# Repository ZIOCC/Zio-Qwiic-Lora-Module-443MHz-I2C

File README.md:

# Zio-Qwiic-Lora-Module-443MHz-I2C

The gateway firmware referred [Sparkfun's QwiicRF](https://github.com/sparkfunx/Qwiic_RF)

> This product can be available for purchase [here](https://www.smart-prototyping.com/Zio-Qwiic-Lora-module-443MHz-I2C).

##### Description

This is a [Qwiic](https://www.smart-prototyping.com/Qwiic.html) version LoRa module, no soldering and jumper wire connections, just [Qwiic cable](https://www.smart-prototyping.com/zio-cables) plugin, and have fun! 

LoRa module is powerful, it can send and receive data packets at up to 10KM distance, and consumes very low power (10mA for receiver, 120mA for transmitter).

LoRa itself is a SPI device, in order to turn it into a I2C device, we added an MCU as the gateway to do the dirty work for you, you just need to use the module’s I2C interface to communicate with the others. It is just that easy.

> Note: This LoRa module is based on the LoRa-01 module, the frequency range is 420 - 450 MHz, check [here](https://www.thethingsnetwork.org/docs/lorawan/frequencies-by-country.html) to see if this can be used in your country.

##### Specification

* Voltage: 3.3V
* Interface: I2C
* I2C Address: 0x35, 0x36 (Default: 0x35)
* Distance: Up to 10KM
* Gateway MCU: ATMEGA328P
* Dimension: 26.0 x 41.6 mm
* Weight: 5.3g

##### Links

* [PCB Source file](https://github.com/ZIOCC/Zio-Qwiic-Lora-Module-443MHz-I2C/tree/master/EAGLE)
* [PCB schematic](https://github.com/ZIOCC/Zio-Qwiic-Lora-Module-443MHz-I2C/blob/master/zio%20qwiic%20lora%20module%20433%20schematic.pdf)
* [Demo code](https://github.com/sparkfun/SparkFun_QwiicRF_Library/)
* [Gateway firmware](https://github.com/ZIOCC/Zio-Qwiic-Lora-Module-443MHz-I2C/tree/master/Gateway_Firmware/Qwiic_RF_I2C_Pairing)

> ###### About Zio
> Zio is a new line of open sourced, compact, and grid layout boards, fully integrated for Arduino and Qwiic ecosystem. Designed ideally for wearables, robotics, small-space limitations or other on the go projects. Check out other awesome Zio products [here](https://www.smart-prototyping.com/Zio).

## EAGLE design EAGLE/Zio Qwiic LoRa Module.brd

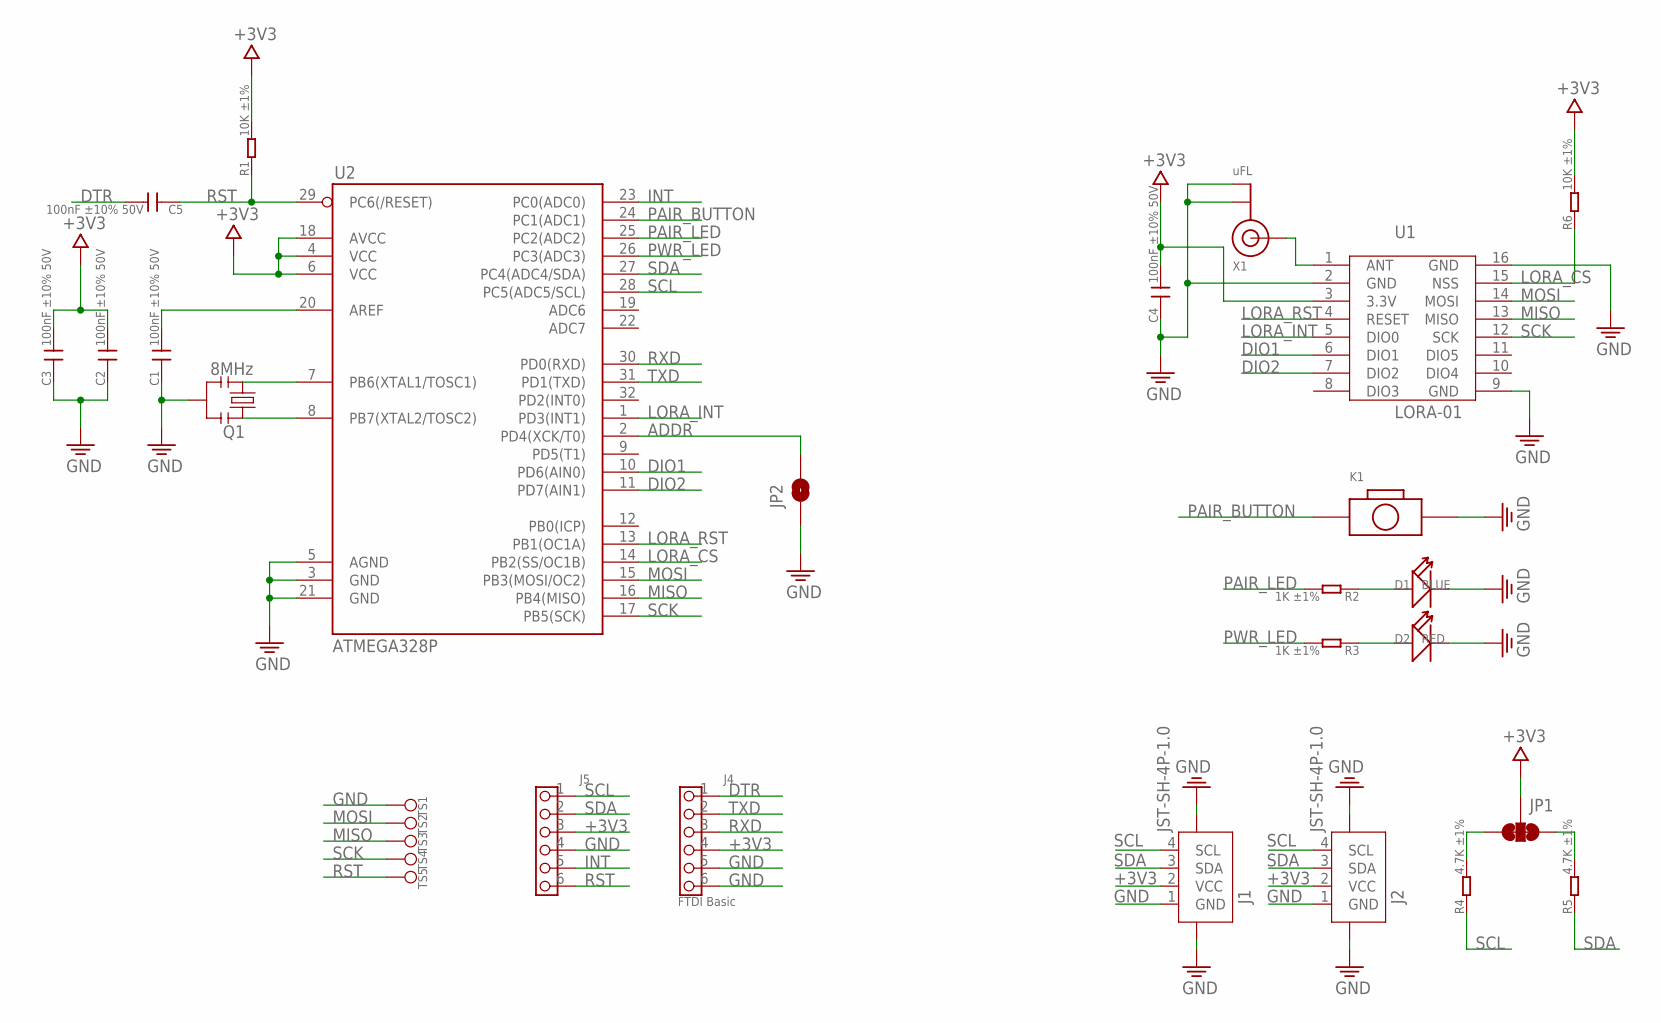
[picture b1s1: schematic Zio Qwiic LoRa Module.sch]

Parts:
C1, C2, C3, C4, C5: 100nF ±10% 50V; C0603
D1: BLUE; LED-0603
D2: RED; LED-0603
J1, J2: JST-SH-4P-1.0; JST-SH-4P
J4: FTDI Basic; 6P-2.54-60/35MIL
J5: HEADER-6P-60/35MIL; 6P-2.54-60/35MIL
JP1: SMT-JUMPER_3_2-NC_TRACE
JP2: JUMPER-SMT_2_NC_PASTE_NOCREM; SMT-JUMPER_2_NC_PASTE_SILK_NOCREM
K1: BOTTON-2PSKRKAEE020; SKRKAEE020
Q1: 8MHz; RESONATOR-SMD
R1, R6: 10K ±1%; R0603
R2, R3: 1K ±1%; R0603
R4, R5: 4.7K ±1%; R0603
TS1, TS2, TS3, TS4, TS5: TEST_POINT35MIL; 1P-35MIL
U1: LORA-01
U2: ATMEGA328P; TQFP32-08
X1: uFL; U.FL

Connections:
+3V3: C2.2, C3.2, C4.2, J1.2 (VCC), J2.2 (VCC), J4.4, J5.3, JP1.2, R1.2, R6.2, U1.3 (3.3V), U2.4 (VCC), U2.6 (VCC), U2.18 (AVCC)
ADDR: JP2.2, U2.2 (PD4(XCK/T0))
DIO1: U1.6 (DIO1), U2.10 (PD6(AIN0))
DIO2: U1.7 (DIO2), U2.11 (PD7(AIN1))
DTR: C5.2, J4.1
GND: C1.1, C2.1, C3.1, C4.1, D1.-, D2.-, J1.1 (GND), J1.NC1 (5), J1.NC2 (6), J2.1 (GND), J2.NC1 (5), J2.NC2 (6), J4.5, J4.6, J5.4, JP2.1, K1.2, Q1.2, TS1.P$1, U1.2 (GND), U1.9 (GND), U1.16 (GND), U2.3 (GND), U2.5 (AGND), U2.21 (GND), X1.1 (GND), X1.2 (GND)
INT: J5.5, U2.23 (PC0(ADC0))
LORA_CS: R6.1, U1.15 (NSS), U2.14 (PB2(SS/OC1B))
LORA_INT: U1.5 (DIO0), U2.1 (PD3(INT1))
LORA_RST: U1.4 (RESET), U2.13 (PB1(OC1A))
MISO: TS3.P$1, U1.13 (MISO), U2.16 (PB4(MISO))
MOSI: TS2.P$1, U1.14 (MOSI), U2.15 (PB3(MOSI/OC2))
unnamed: D1.+, R2.1
unnamed: D2.+, R3.1
unnamed: Q1.3, U2.7 (PB6(XTAL1/TOSC1))
unnamed: Q1.1, U2.8 (PB7(XTAL2/TOSC2))
unnamed: C1.2, U2.20 (AREF)
unnamed: U1.1 (ANT), X1.3 (SIGNAL)
unnamed: JP1.3, R4.2
unnamed: JP1.1, R5.2
PAIR_BUTTON: K1.1, U2.24 (PC1(ADC1))
PAIR_LED: R2.2, U2.25 (PC2(ADC2))
PWR_LED: R3.2, U2.26 (PC3(ADC3))
RST: C5.1, J5.6, R1.1, TS5.P$1, U2.29 (PC6(/RESET))
RXD: J4.3, U2.30 (PD0(RXD))
SCK: TS4.P$1, U1.12 (SCK), U2.17 (PB5(SCK))
SCL: J1.4 (SCL), J2.4 (SCL), J5.1, R4.1, U2.28 (PC5(ADC5/SCL))
SDA: J1.3 (SDA), J2.3 (SDA), J5.2, R5.1, U2.27 (PC4(ADC4/SDA))
TXD: J4.2, U2.31 (PD1(TXD))

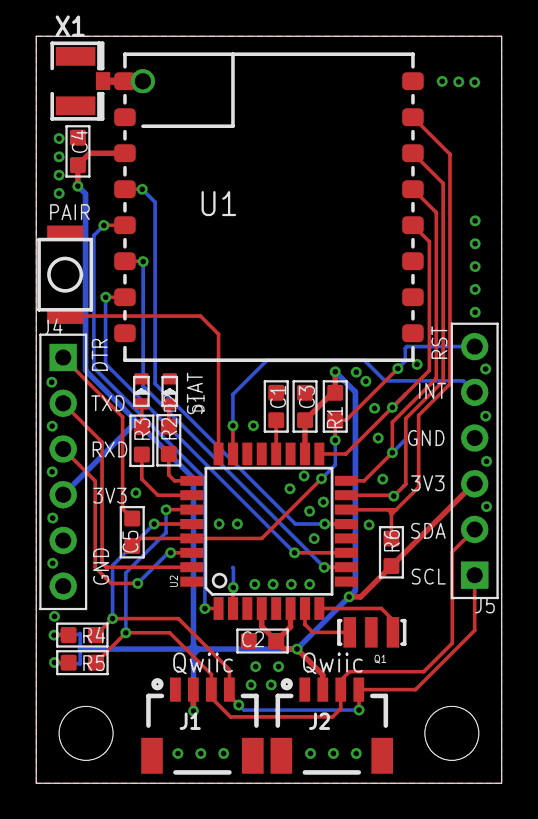
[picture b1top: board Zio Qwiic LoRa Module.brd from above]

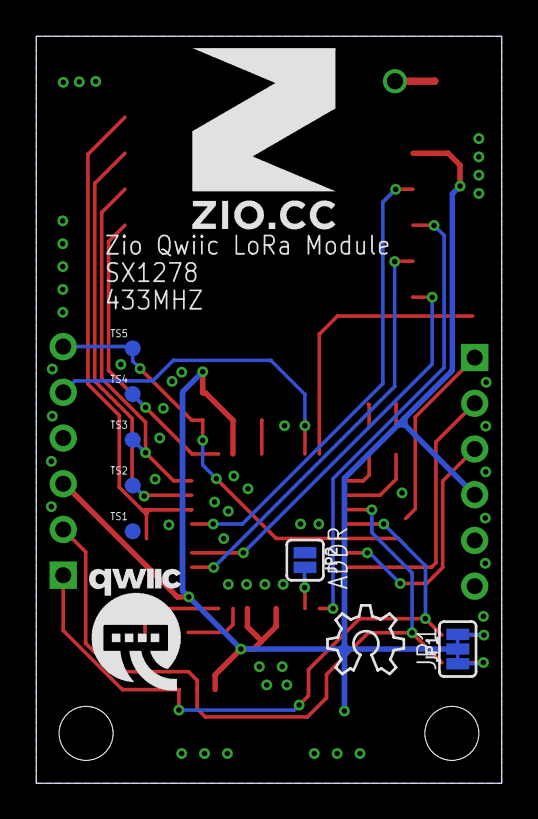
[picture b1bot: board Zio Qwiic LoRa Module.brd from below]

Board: 2 copper layers, 25.9 x 41.5 mm, 32 parts (10 on the bottom side), 29 nets.

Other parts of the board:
U$10: 10MM
U$11: QWIIC-LOGO-MEDIUM
U$12: OSHW_6X150_NOTEXT

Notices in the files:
parts and their libraries:
microbuilder: This work is placed in the public domain, and may be freely used for commercial and non-commercial work with the following conditions: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
